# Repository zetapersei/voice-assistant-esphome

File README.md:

# ESPHome voice assistant for Home Assistant

A hands-free voice assistant based on the ESP32-S3. The device detects the
**“Okay Nabu”** wake word locally; Home Assistant runs the Assist pipeline for
speech recognition, conversation, and speech synthesis.

## Hardware

### Components and requirements

- **ESP32-S3 DevKitC-1** board with an **N8R8** module: 8 MB flash and 8 MB
  octal PSRAM. This configuration uses ESP-IDF and requires octal PSRAM.
- **INMP441** I²S microphone module. It runs on 3.3 V and sends digital audio
  to the ESP32 data pin.
- **MAX98357A** I²S amplifier module, powered from 5 V. It receives digital
  audio from the ESP32 and directly drives the speaker.
- **4 or 8 Ω** passive speaker rated for at least **3 W**.
- Stable **5 V, at least 1 A** USB supply, hookup wires, and optionally a
  perfboard or PCB.

The INMP441 and MAX98357A modules must support the ESP32's 3.3 V logic
levels. Pin labels may vary; check the markings and datasheets for the actual
modules before wiring them.

The KiCad design files are in [`voiceass-kicad/`](voiceass-kicad/):
[`voiceass-kicad.kicad_sch`](voiceass-kicad/voiceass-kicad.kicad_sch) is the
schematic and [`voiceass-kicad.kicad_pcb`](voiceass-kicad/voiceass-kicad.kicad_pcb)
is the PCB layout.

### Wiring

| Signal | ESP32-S3 DevKitC-1 | INMP441 | MAX98357A |
|---|---|---|---|
| Bit clock (BCLK) | GPIO5 | SCK | BCLK |
| Word clock (LRCLK/WS) | GPIO6 | WS | LRC |
| Microphone data | GPIO4 | SD | — |
| Speaker data | GPIO16 | — | DIN |
| Microphone power | 3V3 | VDD | — |
| Amplifier power | 5V | — | VIN |
| Common ground | GND | GND | GND |
| Microphone channel select | GND | L/R | — |
| Amplifier enable/channel select | 3V3 | — | SD_MODE |
| Amplifier gain setting | 5V | — | GAIN_SLOT |
| Amplifier output | — | — | SPK+ and SPK− to speaker |

BCLK, LRCLK, and GND are shared by both I²S modules. Connecting the
microphone's L/R pin to GND selects the left channel, matching `channel: left`
in the configuration. Power the microphone from 3.3 V and the amplifier from
5 V; do not power the microphone from 5 V. Connect the speaker's two
terminals only to SPK+ and SPK−: this is a bridge-tied output, so neither
speaker terminal should be connected to GND or an ESP32 GPIO.

Connect `SD_MODE` to 3V3 to enable the amplifier and select the left audio
channel; pulling it low shuts the amplifier down. Connect `GAIN_SLOT` to 5V
for 6 dB gain. In the current KiCad files, `GAIN_SLOT` is connected to +5V.

Use a common ground for the board, microphone, and amplifier. Check the
development board pinout before applying power, and never connect the
amplifier output directly to the ESP32. Use a stable supply and wiring sized
for the amplifier's 5 V current draw to help prevent resets and audio noise.

## Configuration

1. Copy `voice-assistant.yaml` to the ESPHome configuration directory used by
   Home Assistant.
2. In ESPHome's `secrets.yaml`, define `wifi_ssid`, `wifi_password`,
   `fallback_password`, and `api_encryption_key`. Choose strong passwords for
   Wi-Fi and the fallback access point. `api_encryption_key` must be a
   Base64-encoded, 32-byte ESPHome API key; you can generate one with
   `openssl rand -base64 32`. The API key protects both the native Home
   Assistant connection and OTA updates via ESPHome's recommended encrypted OTA
   flow. Do not share or commit the secrets file.
3. Validate and compile with `esphome config voice-assistant.yaml` and
   `esphome compile voice-assistant.yaml`, then install the firmware over USB.
4. Add the discovered ESPHome device in Home Assistant. Configure an Assist
   pipeline in Italian with an STT engine, conversation agent, and TTS engine.
5. Say **“Okay Nabu”** and wait for the listening cue before speaking.

Wi-Fi `power_save_mode: none` disables radio power saving, reducing latency
during audio use at the cost of higher power consumption. The microphone and
wake-word detection run on the device; speech recognition and responses are
handled by Home Assistant's pipeline. Set the Assist pipeline language
separately in Home Assistant.

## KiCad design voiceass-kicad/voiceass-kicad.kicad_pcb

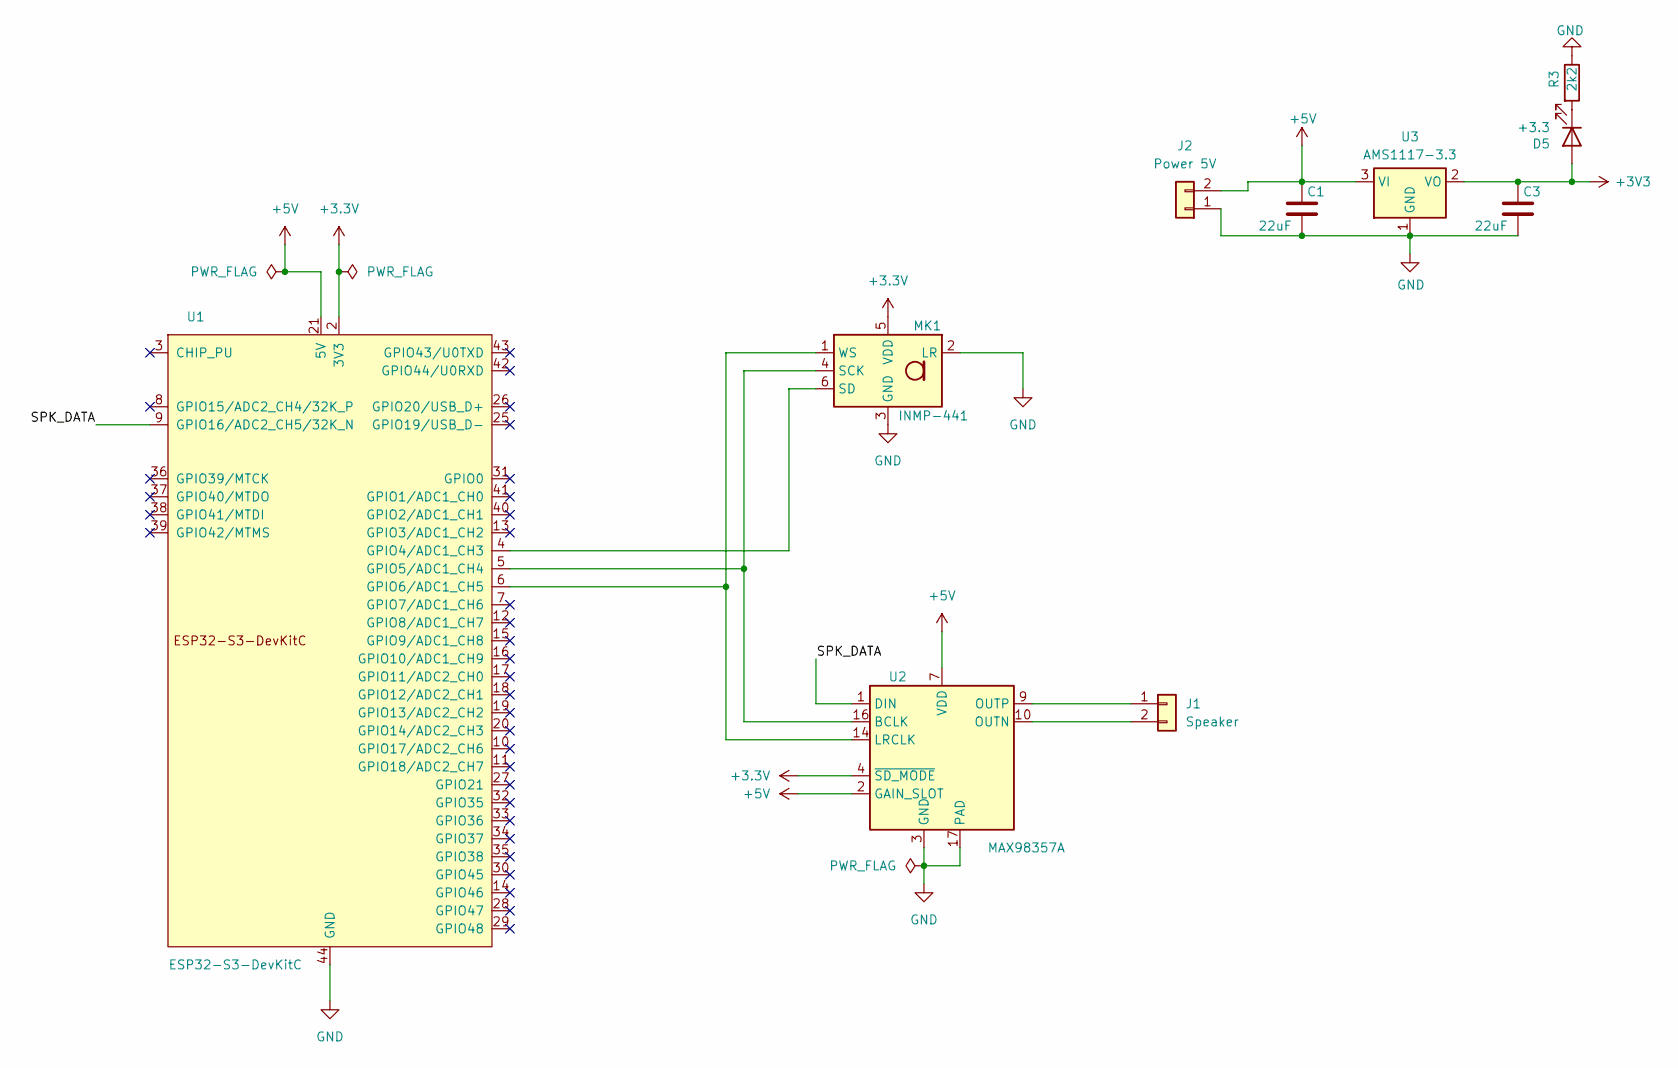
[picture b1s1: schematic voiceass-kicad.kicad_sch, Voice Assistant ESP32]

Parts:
C1, C3: 22uF; C_1210_3225Metric
D5: +3.3; LED_1206_3216Metric
J1: Speaker; PinHeader_1x02_P2.54mm_Vertical
J2: Power 5V; PinHeader_1x02_P2.54mm_Vertical
MK1: INMP-441; InvenSense_ICS-43434-6_3.5x2.65mm
R3: 2k2; R_1206_3216Metric
U1: ESP32-S3-DevKitC
U2: MAX98357A; TQFN-16-1EP_3x3mm_P0.5mm_EP1.23x1.23mm
U3: AMS1117-3.3; SOT-223-3_TabPin2

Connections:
+3.3V: MK1.5 (VDD), U1.1 (3V3), U1.2 (3V3), U2.4 (~SD_MODE)
+3V3: C3.1, D5.2 (A), U3.2 (VO)
+5V: C1.1, J2.2, U1.21 (5V), U2.2 (GAIN_SLOT), U2.7 (VDD), U2.8 (VDD), U3.3 (VI)
/SPK_DATA: U1.9 (GPIO16/ADC2_CH5/32K_N), U2.1 (DIN)
GND: C1.2, C3.2, J2.1, MK1.2 (LR), MK1.3 (GND), R3.1, U1.22 (GND), U1.23 (GND), U1.24 (GND), U1.44 (GND), U2.3 (GND), U2.11 (GND), U2.15 (GND), U2.17 (PAD), U3.1 (GND)
unnamed: D5.1 (K), R3.2
unnamed: J1.1, U2.9 (OUTP)
unnamed: J1.2, U2.10 (OUTN)
unnamed: MK1.4 (SCK), U1.5 (GPIO5/ADC1_CH4), U2.16 (BCLK)
unnamed: MK1.6 (SD), U1.4 (GPIO4/ADC1_CH3)
unnamed: MK1.1 (WS), U1.6 (GPIO6/ADC1_CH5), U2.14 (LRCLK)

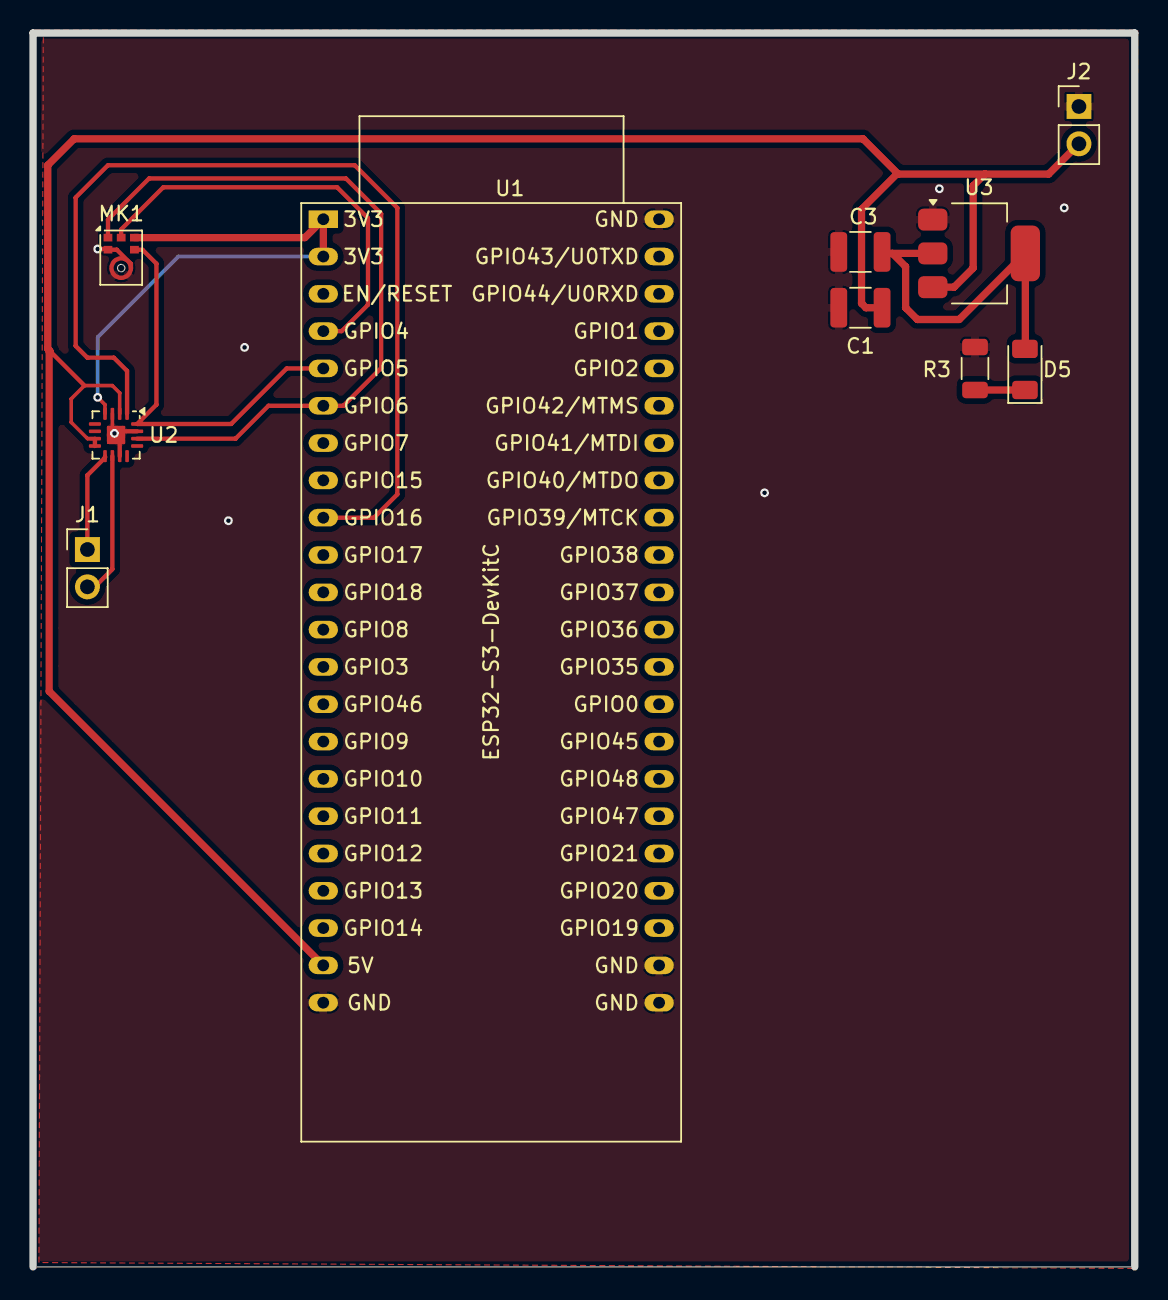
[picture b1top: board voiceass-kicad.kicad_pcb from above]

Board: 2 copper layers, 75.0 x 84.0 mm, 10 parts (0 on the bottom side), 11 nets.

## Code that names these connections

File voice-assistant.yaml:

esphome:
  name: assistente-vocale
  friendly_name: Assistente Vocale
  min_version: 2025.5.0

esp32:
  board: esp32-s3-devkitc-1
  flash_size: 8MB
  framework:
    type: esp-idf

psram:
  mode: octal
  speed: 80MHz

logger:
  level: INFO

api:
  encryption:
    key: !secret api_encryption_key

ota:
  - platform: esphome

wifi:
  ssid: !secret wifi_ssid
  password: !secret wifi_password
  power_save_mode: none
  ap:
    ssid: "Assistente-Vocale Fallback"
    password: !secret fallback_password

captive_portal:

i2s_audio:
  - id: i2s_bus
    i2s_lrclk_pin: GPIO6
    i2s_bclk_pin: GPIO5

microphone:
  - platform: i2s_audio
    id: microfono_i2s
    i2s_audio_id: i2s_bus
    i2s_din_pin: GPIO4
    adc_type: external
    # INMP441: connect L/R to GND to select the left channel.
    channel: left
    sample_rate: 16000
    bits_per_sample: 32bit

speaker:
  - platform: i2s_audio
    id: altoparlante_i2s
    i2s_audio_id: i2s_bus
    i2s_dout_pin: GPIO16
    dac_type: external
    channel: mono
    bits_per_sample: 16bit
    buffer_duration: 100ms

micro_wake_word:
  microphone:
    microphone: microfono_i2s
    channels: 0
    gain_factor: 4
  task_stack_in_psram: true
  models:
    - model: okay_nabu
  on_wake_word_detected:
    - voice_assistant.start:
        wake_word: !lambda return wake_word;

voice_assistant:
  microphone: microfono_i2s
  speaker: altoparlante_i2s
  use_wake_word: true
  on_end:
    - micro_wake_word.start:
  on_error:
    - micro_wake_word.start:
